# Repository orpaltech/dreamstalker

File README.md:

# dreamstalker

This device is designed to assist with lucid dreaming. The idea comes from this site: https://smartelectron.ru/projects/pribor-dlya-osoznannyh-snovidenij-dreamstalker-pro.

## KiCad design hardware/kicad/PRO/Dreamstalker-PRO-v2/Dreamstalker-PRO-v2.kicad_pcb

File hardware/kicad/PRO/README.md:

Dreamstalker PRO
------

The hardware to control your dreams. The author's resource is https://www.razrabotka.pro/single-post/pribor-dlya-osoznannyh-snovidenij-dreamstalker-pro

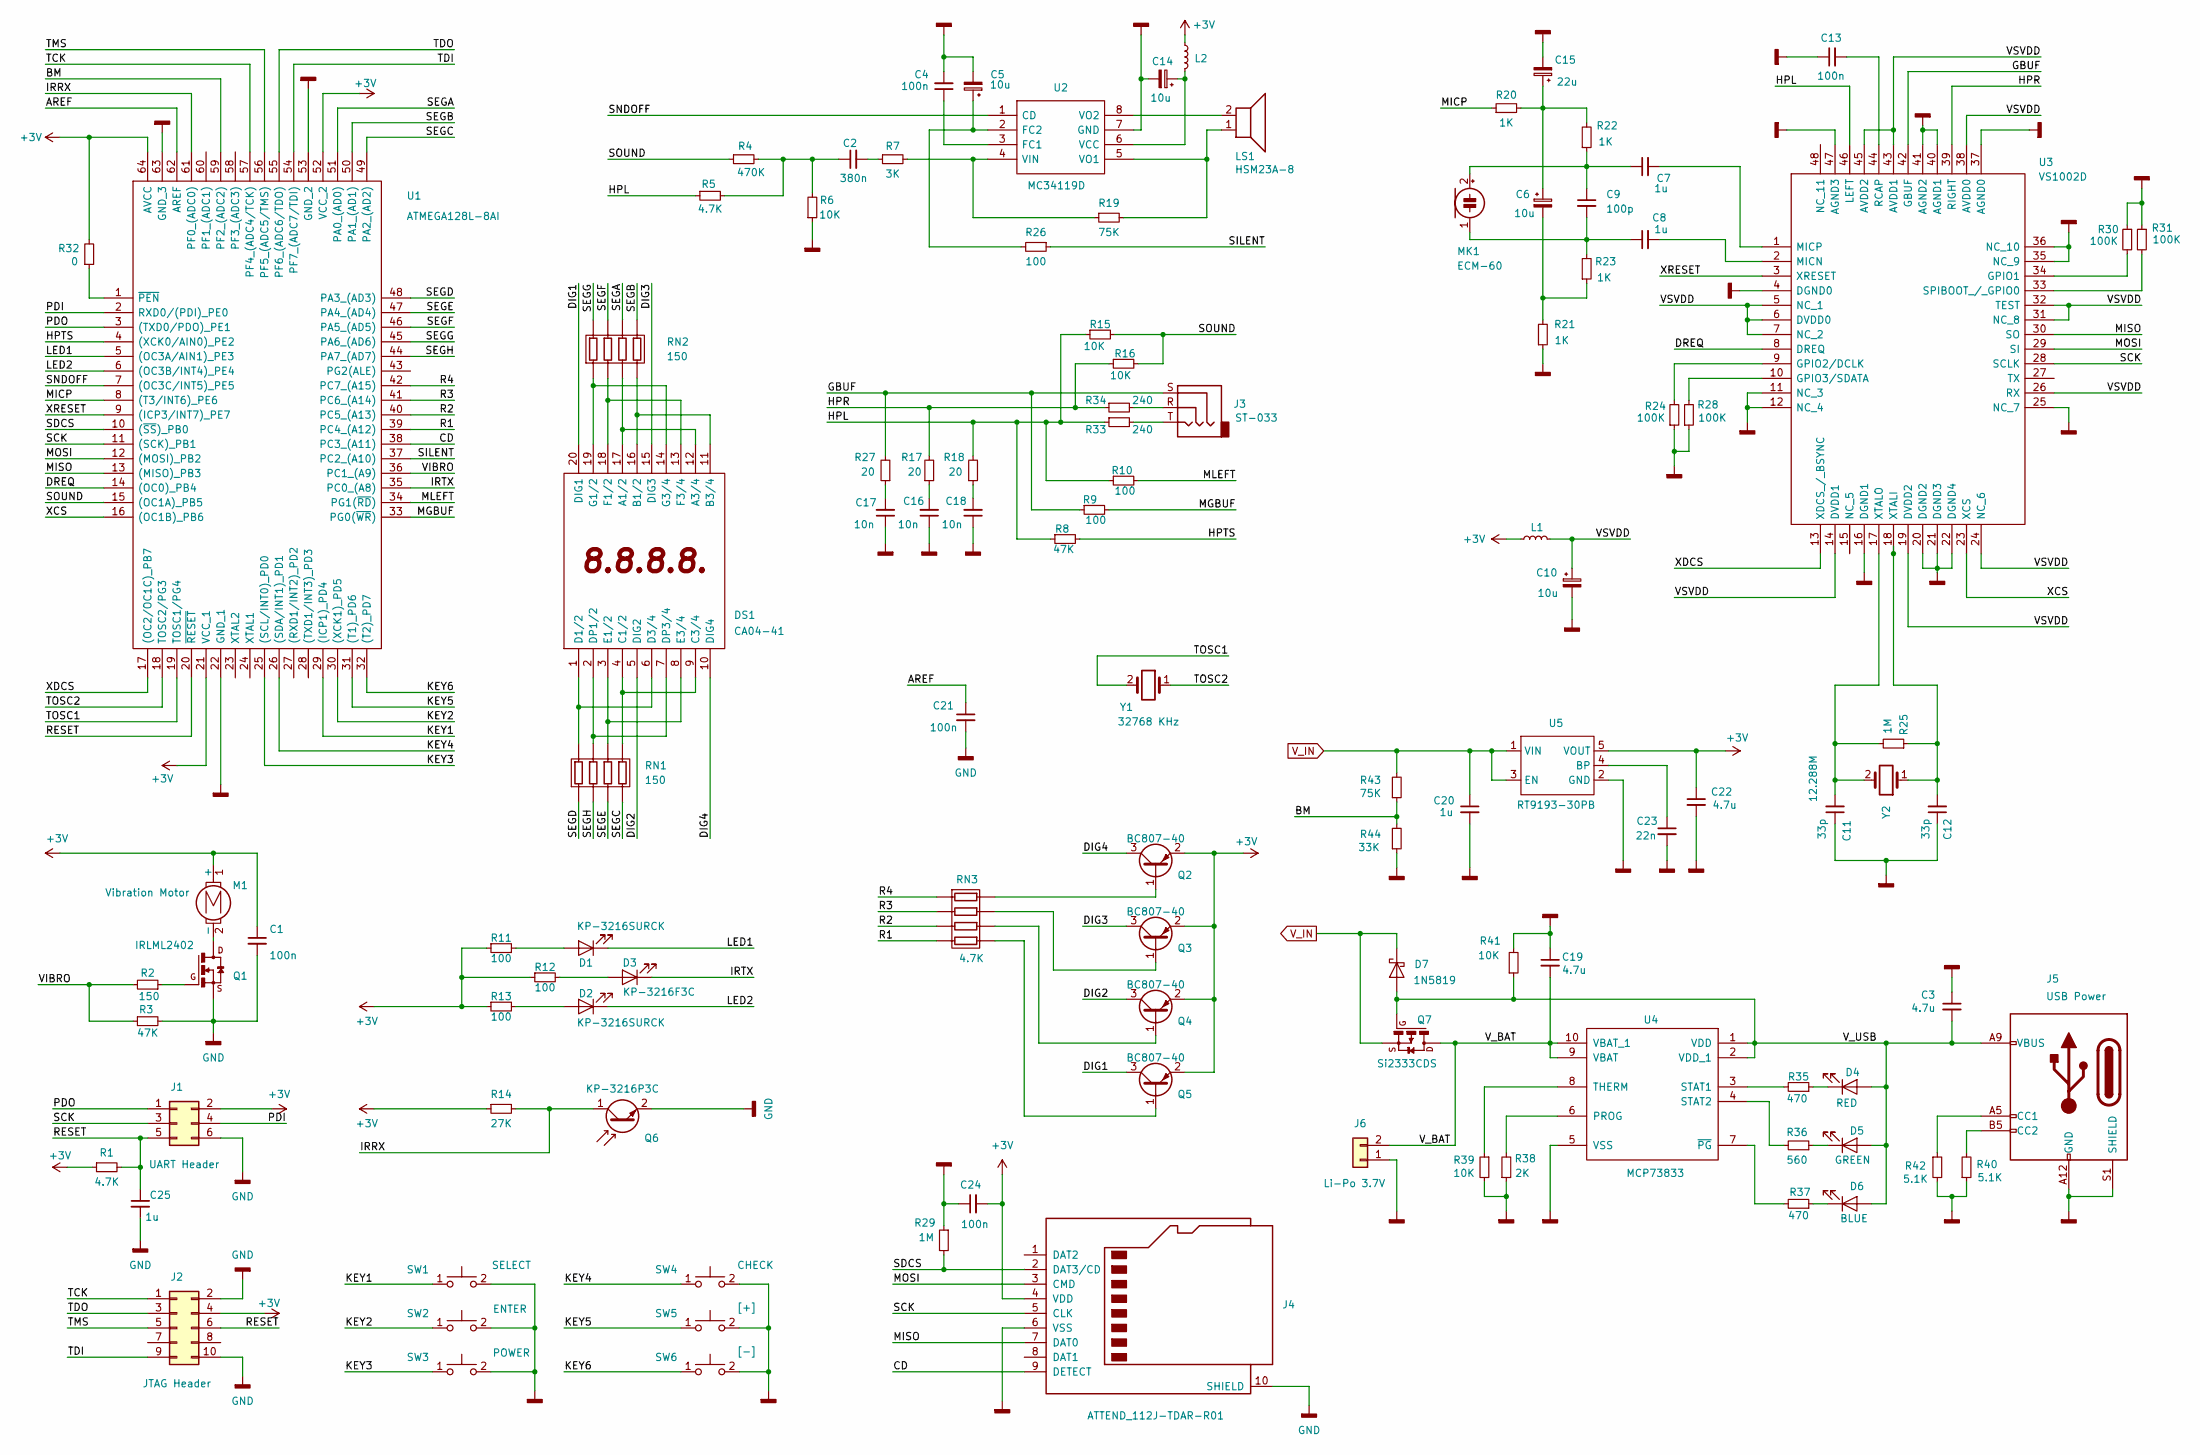
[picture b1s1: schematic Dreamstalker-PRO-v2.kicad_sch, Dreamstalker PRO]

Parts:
C1, C4, C13, C21, C24: 100n; C_0805_2012Metric
C2: 380n; C_0805_2012Metric
C3, C19, C22: 4.7u; C_0805_2012Metric
C5, C6, C10, C14: 10u; CP_EIA-3216-18_Kemet-A
C7, C8, C20, C25: 1u; C_0805_2012Metric
C9: 100p; C_0805_2012Metric
C11, C12: 33p; C_0805_2012Metric
C15: 22u; CP_EIA-3216-18_Kemet-A
C16, C17, C18: 10n; C_0805_2012Metric
C23: 22n; C_0805_2012Metric
D1, D2: KP-3216SURCK; LEDC3216X110N-TH
D3: KP-3216F3C; LEDC3216X110N-TH
D4: RED; LED_0805_2012Metric
D5: GREEN; LED_0805_2012Metric
D6: BLUE; LED_0805_2012Metric
D7: 1N5819; D_SOD-323_HandSoldering
DS1: CA04-41; Manufacturer_Part_Number CA04-41
J1: UART Header; PinHeader_2x03_P2.54mm_Vertical
J2: JTAG Header; PinHeader_2x05_P2.54mm_Vertical
J3: ST-033; DCI_Phone_Jack_3.5mm_ST-033
J4: ATTEND_112J-TDAR-R01; Manufacturer_Part_Number 112J-TDAR-R01
J5: USB Power; USB_C_Receptacle_GCT_USB4125-xx-x_6P_TopMnt_Horizontal
J6: Li-Po 3.7V; JST_PH_B2B-PH-K_1x02_P2.00mm_Vertical
L1, L2: L_Small; L_0805_2012Metric
LS1: HSM23A-8; Buzzer_23x11.5RM10
M1: Vibration Motor; VIBRO-MOTOR_SMD
MK1: ECM-60; JININ_ELECTRET_CONDENSER_MICROPHONE_ECM-60
Q1: IRLML2402; SOT95P237X112-3N
Q2, Q3, Q4, Q5: BC807-40; SOT95P230X110-3N
Q6: KP-3216P3C; LEDC3216X130N-TH
Q7: Si2333CDS; SOT-23
R1, R5: 4.7K; R_0603_1608Metric
R2: 150; R_0603_1608Metric
R3, R8: 47K; R_0603_1608Metric
R4: 470K; R_0603_1608Metric
R6, R15, R16, R39, R41: 10K; R_0603_1608Metric
R7: 3K; R_0603_1608Metric
R9, R10, R11, R12, R13, R26: 100; R_0603_1608Metric
R14: 27K; R_0603_1608Metric
R17, R18, R27: 20; R_0603_1608Metric
R19, R43: 75K; R_0603_1608Metric
R20, R21, R22, R23: 1K; R_0603_1608Metric
R24, R28, R30, R31: 100K; R_0603_1608Metric
R25, R29: 1M; R_0603_1608Metric
R32: 0; R_0603_1608Metric
R33, R34: 240; R_0603_1608Metric
R35, R37: 470; R_0603_1608Metric
R36: 560; R_0603_1608Metric
R38: 2K; L_0603_1608Metric
R40, R42: 5.1K; R_0603_1608Metric
R44: 33K; R_0603_1608Metric
RN1, RN2: 150; R_Array_Convex_4x0603
RN3: 4.7K; R_Array_Convex_4x0603
SW1: SELECT; SW_PUSH_6mm
SW2: ENTER; SW_PUSH_6mm
SW3: POWER; SW_PUSH_6mm
SW4: CHECK; SW_PUSH_6mm
SW5: [+]; SW_PUSH_6mm
SW6: [-]; SW_PUSH_6mm
U1: ATMEGA128L-8AI; QFP80P1600X1600X120-64N; Manufacturer_Part_Number ATMEGA128L-8AI
U2: MC34119D; SOIC127P600X175-8N; Manufacturer_Part_Number MC34119D
U3: VS1002D; QFP50P900X900X160-48N; Manufacturer_Part_Number VS1002D
U4: MCP73833; SOP50P490X110-10N; Manufacturer_Part_Number MCP73833-FCI/UN
U5: RT9193-30PB; SOT-23-5; Manufacturer_Part_Number RT9193
Y1: 32768 KHz; Crystal_SMD_3215-2Pin_3.2x1.5mm
Y2: 12.288M; Crystal_SMD_5032-2Pin_5.0x3.2mm

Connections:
+3V: C1.1, C22.1, C24.2, J1.2, J2.4, J4.4 (VDD), L1.1, L2.1, M1.1 (+), Q2.2 (E), Q3.2 (E), Q4.2 (E), Q5.2 (E), R1.1, R11.1, R12.1, R13.1, R14.1, R32.2, U1.21 (VCC_1), U1.52 (VCC_2), U1.64 (AVCC), U5.5 (VOUT)
/AREF: C21.1, U1.62 (AREF)
/BM: R43.1, R44.2, U1.59 (PF2_(ADC2))
/CD: J4.9 (DETECT), U1.38 (PC3_(A11))
/DIG1: DS1.20 (DIG1), Q5.3 (C)
/DIG2: DS1.5 (DIG2), Q4.3 (C)
/DIG3: DS1.15 (DIG3), Q3.3 (C)
/DIG4: DS1.10 (DIG4), Q2.3 (C)
/DREQ: U1.14 ((OC0)_PB4), U3.8 (DREQ)
/GBUF: J3.S, R9.1, R27.2, U3.42 (GBUF)
/HPL: R5.1, R8.1, R10.1, R15.1, R18.2, R33.1, U3.46 (LEFT)
/HPR: R16.1, R17.2, R34.1, U3.39 (RIGHT)
/HPTS: R8.2, U1.4 ((XCK0/AIN0)_PE2)
/IRRX: Q6.1 (C), R14.2, U1.61 (PF0_(ADC0))
/IRTX: D3.1 (K), U1.35 (PC0_(A8))
/KEY1: SW1.1, U1.29 ((ICP1)_PD4)
/KEY2: SW2.1, U1.30 ((XCK1)_PD5)
/KEY3: SW3.1, U1.25 ((SCL/INT0)_PD0)
/KEY4: SW4.1, U1.26 ((SDA/INT1)_PD1)
/KEY5: SW5.1, U1.31 ((T1)_PD6)
/KEY6: SW6.1, U1.32 ((T2)_PD7)
/LED1: D1.1 (K), U1.5 ((OC3A/AIN1)_PE3)
/LED2: D2.1 (K), U1.6 ((OC3B/INT4)_PE4)
/MGBUF: R9.2, U1.33 (PG0(~WR))
/MICP: R20.1, U1.8 ((T3/INT6)_PE6)
/MISO: J4.7 (DAT0), U1.13 ((MISO)_PB3), U3.30 (SO)
/MLEFT: R10.2, U1.34 (PG1(~RD))
/MOSI: J4.3 (CMD), U1.12 ((MOSI)_PB2), U3.29 (SI)
/PDI: J1.4, U1.2 (RXD0/(PDI)_PE0)
/PDO: J1.1, U1.3 ((TXD0/PDO)_PE1)
/R1: RN3.4 (R4.1), U1.39 (PC4_(A12))
/R2: RN3.3 (R3.1), U1.40 (PC5_(A13))
/R3: RN3.2 (R2.1), U1.41 (PC6_(A14))
/R4: RN3.1 (R1.1), U1.42 (PC7_(A15))
/RESET: C25.1, J1.5, J2.6, R1.2, U1.20 (~RESET)
/SCK: J1.3, J4.5 (CLK), U1.11 ((SCK)_PB1), U3.28 (SCLK)
/SDCS: J4.2 (DAT3/CD), R29.2, U1.10 ((~SS)_PB0)
/SEGA: RN2.6 (R3.2), U1.51 (PA0_(AD0))
/SEGB: RN2.5 (R4.2), U1.50 (PA1_(AD1))
/SEGC: RN1.4 (R4.1), U1.49 (PA2_(AD2))
/SEGD: RN1.1 (R1.1), U1.48 (PA3_(AD3))
/SEGE: RN1.3 (R3.1), U1.47 (PA4_(AD4))
/SEGF: RN2.7 (R2.2), U1.46 (PA5_(AD5))
/SEGG: RN2.8 (R1.2), U1.45 (PA6_(AD6))
/SEGH: RN1.2 (R2.1), U1.44 (PA7_(AD7))
/SILENT: R26.1, U1.37 (PC2_(A10))
/SNDOFF: U1.7 ((OC3C/INT5)_PE5), U2.1 (CD)
/SOUND: R4.1, R15.2, R16.2, U1.15 ((OC1A)_PB5)
/TCK: J2.1, U1.57 (PF4_(ADC4/TCK))
/TDI: J2.9, U1.54 (PF7_(ADC7/TDI))
/TDO: J2.3, U1.55 (PF6_(ADC6/TDO))
/TMS: J2.5, U1.56 (PF5_(ADC5/TMS))
/TOSC1: U1.19 (TOSC1/PG4), Y1.2
/TOSC2: U1.18 (TOSC2/PG3), Y1.1
/VIBRO: R2.2, R3.1, U1.36 (PC1_(A9))
/VSVDD: C10.1, L1.2, U3.5 (NC_1), U3.6 (DVDD0), U3.7 (NC_2), U3.14 (DVDD1), U3.19 (DVDD2), U3.24 (NC_6), U3.26 (RX), U3.31 (NC_8), U3.32 (TEST), U3.38 (AVDD0), U3.43 (AVDD1), U3.45 (AVDD2)
/V_BAT: C19.2, J6.2, Q7.3 (D), U4.9 (VBAT), U4.10 (VBAT_1)
/V_USB: C3.2, D4.2 (A), D5.2 (A), D6.2 (A), D7.2 (A), J5.A9 (VBUS), J5.B9 (VBUS), Q7.1 (G), R41.1, U4.1 (VDD), U4.2 (VDD_1)
/XCS: U1.16 ((OC1B)_PB6), U3.23 (XCS)
/XDCS: U1.17 ((OC2/OC1C)_PB7), U3.13 (XDCS_/_BSYNC)
/XRESET: U1.9 ((ICP3/INT7)_PE7), U3.3 (XRESET)
GND: C1.2, C3.1, C4.2, C5.2, C10.2, C11.1, C12.1, C13.1, C14.2, C15.2, C16.1, C17.1, C18.1, C19.1, C20.2, C21.2, C22.2, C23.2, C24.1, C25.2, J1.6, J2.2, J2.10, J4.6 (VSS), J4.10 (SHIELD), J5.A12 (GND), J5.B12 (GND), J5.S1 (SHIELD), J6.1, Q1.2 (S), Q6.2 (E), R3.2, R6.1, R21.1, R24.1, R28.1, R29.1, R30.1, R31.1, R38.1, R39.2, R40.1, R41.2, R42.2, R44.1, SW1.2, SW2.2, SW3.2, SW4.2, SW5.2, SW6.2, U1.22 (GND_1), U1.53 (GND_2), U1.63 (GND_3), U2.7 (GND), U3.4 (DGND0), U3.11 (NC_3), U3.12 (NC_4), U3.16 (DGND1), U3.20 (DGND2), U3.21 (DGND3), U3.22 (DGND4), U3.25 (NC_7), U3.35 (NC_9), U3.36 (NC_10), U3.37 (AGND0), U3.40 (AGND1), U3.41 (AGND2), U3.47 (AGND3), U4.5 (VSS), U5.2 (GND)
unnamed: C2.1, R4.2, R5.2, R6.2
unnamed: C2.2, R7.1
unnamed: C6.2, R21.2, R23.1
unnamed: C6.1, C15.1, R20.2, R22.2
unnamed: C16.2, R17.1
unnamed: C17.2, R27.1
unnamed: C18.2, R18.1
unnamed: D1.2 (A), R11.2
unnamed: D2.2 (A), R13.2
unnamed: D3.2 (A), R12.2
unnamed: D4.1 (K), R35.1
unnamed: D5.1 (K), R36.1
unnamed: D6.1 (K), R37.1
unnamed: DS1.12 (A3/4), DS1.17 (A1/2), RN2.3 (R3.1)
unnamed: DS1.11 (B3/4), DS1.16 (B1/2), RN2.4 (R4.1)
unnamed: DS1.4 (C1/2), DS1.9 (C3/4), RN1.5 (R4.2)
unnamed: DS1.1 (D1/2), DS1.6 (D3/4), RN1.8 (R1.2)
unnamed: DS1.2 (DP1/2), DS1.7 (DP3/4), RN1.7 (R2.2)
unnamed: DS1.3 (E1/2), DS1.8 (E3/4), RN1.6 (R3.2)
unnamed: DS1.13 (F3/4), DS1.18 (F1/2), RN2.2 (R2.1)
unnamed: DS1.14 (G3/4), DS1.19 (G1/2), RN2.1 (R1.1)
unnamed: J3.R, R34.2
unnamed: J3.T, R33.2
unnamed: J5.A5 (CC1), R42.1
unnamed: J5.B5 (CC2), R40.2
unnamed: M1.2 (-), Q1.3 (D)
unnamed: C7.1, C9.1, MK1.2 (+), R22.1
unnamed: C8.1, C9.2, MK1.1 (-), R23.2
unnamed: Q1.1 (G), R2.1
unnamed: Q2.1 (B), RN3.8 (R1.2)
unnamed: Q3.1 (B), RN3.7 (R2.2)
unnamed: Q4.1 (B), RN3.6 (R3.2)
unnamed: Q5.1 (B), RN3.5 (R4.2)
unnamed: R32.1, U1.1 (~PEN)
unnamed: C4.1, U2.3 (FC1)
unnamed: C5.1, R26.2, U2.2 (FC2)
unnamed: C14.1, L2.2, U2.6 (VCC)
unnamed: R7.2, R19.1, U2.4 (VIN)
unnamed: LS1.1, R19.2, U2.5 (VO1)
unnamed: LS1.2, U2.8 (VO2)
unnamed: R30.2, U3.34 (GPIO1)
unnamed: R24.2, U3.9 (GPIO2/DCLK)
unnamed: R28.2, U3.10 (GPIO3/SDATA)
unnamed: C8.2, U3.2 (MICN)
unnamed: C7.2, U3.1 (MICP)
unnamed: C13.2, U3.44 (RCAP)
unnamed: R31.2, U3.33 (SPIBOOT_/_GPIO0)
unnamed: C12.2, R25.1, U3.18 (XTALI), Y2.1
unnamed: C11.2, R25.2, U3.17 (XTALO), Y2.2
unnamed: R38.2, U4.6 (PROG)
unnamed: R35.2, U4.3 (STAT1)
unnamed: R36.2, U4.4 (STAT2)
unnamed: R39.1, U4.8 (THERM)
unnamed: R37.2, U4.7 (~PG)
unnamed: C23.1, U5.4 (BP)
V_IN: C20.1, D7.1 (K), Q7.2 (S), R43.2, U5.1 (VIN), U5.3 (EN)

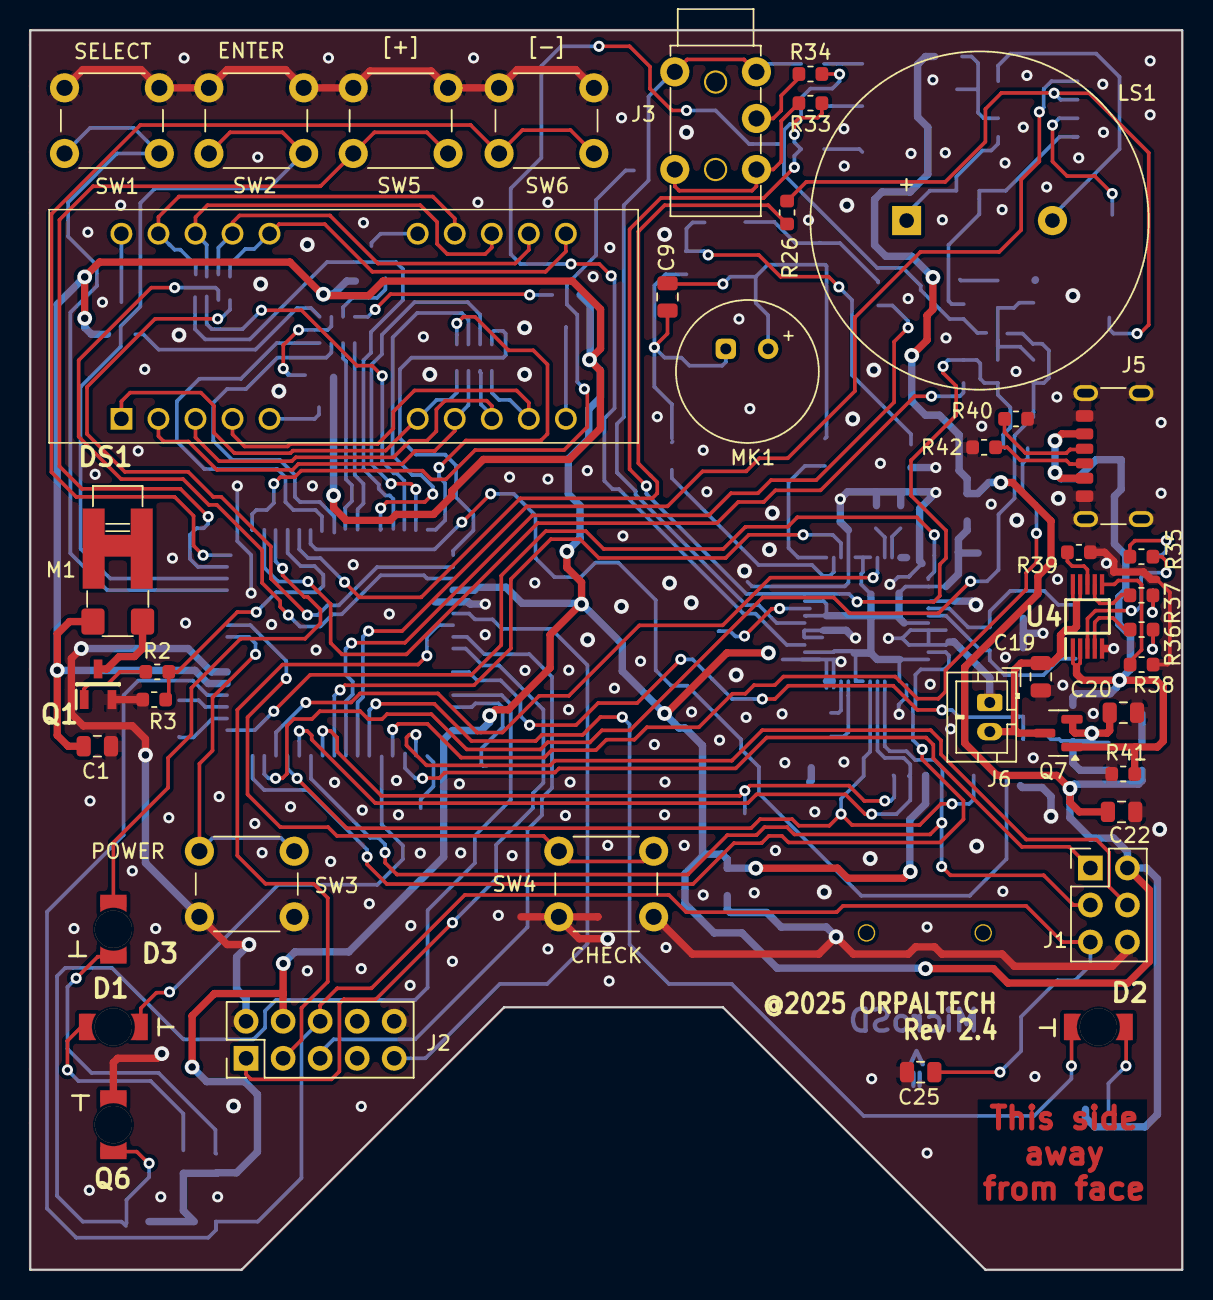
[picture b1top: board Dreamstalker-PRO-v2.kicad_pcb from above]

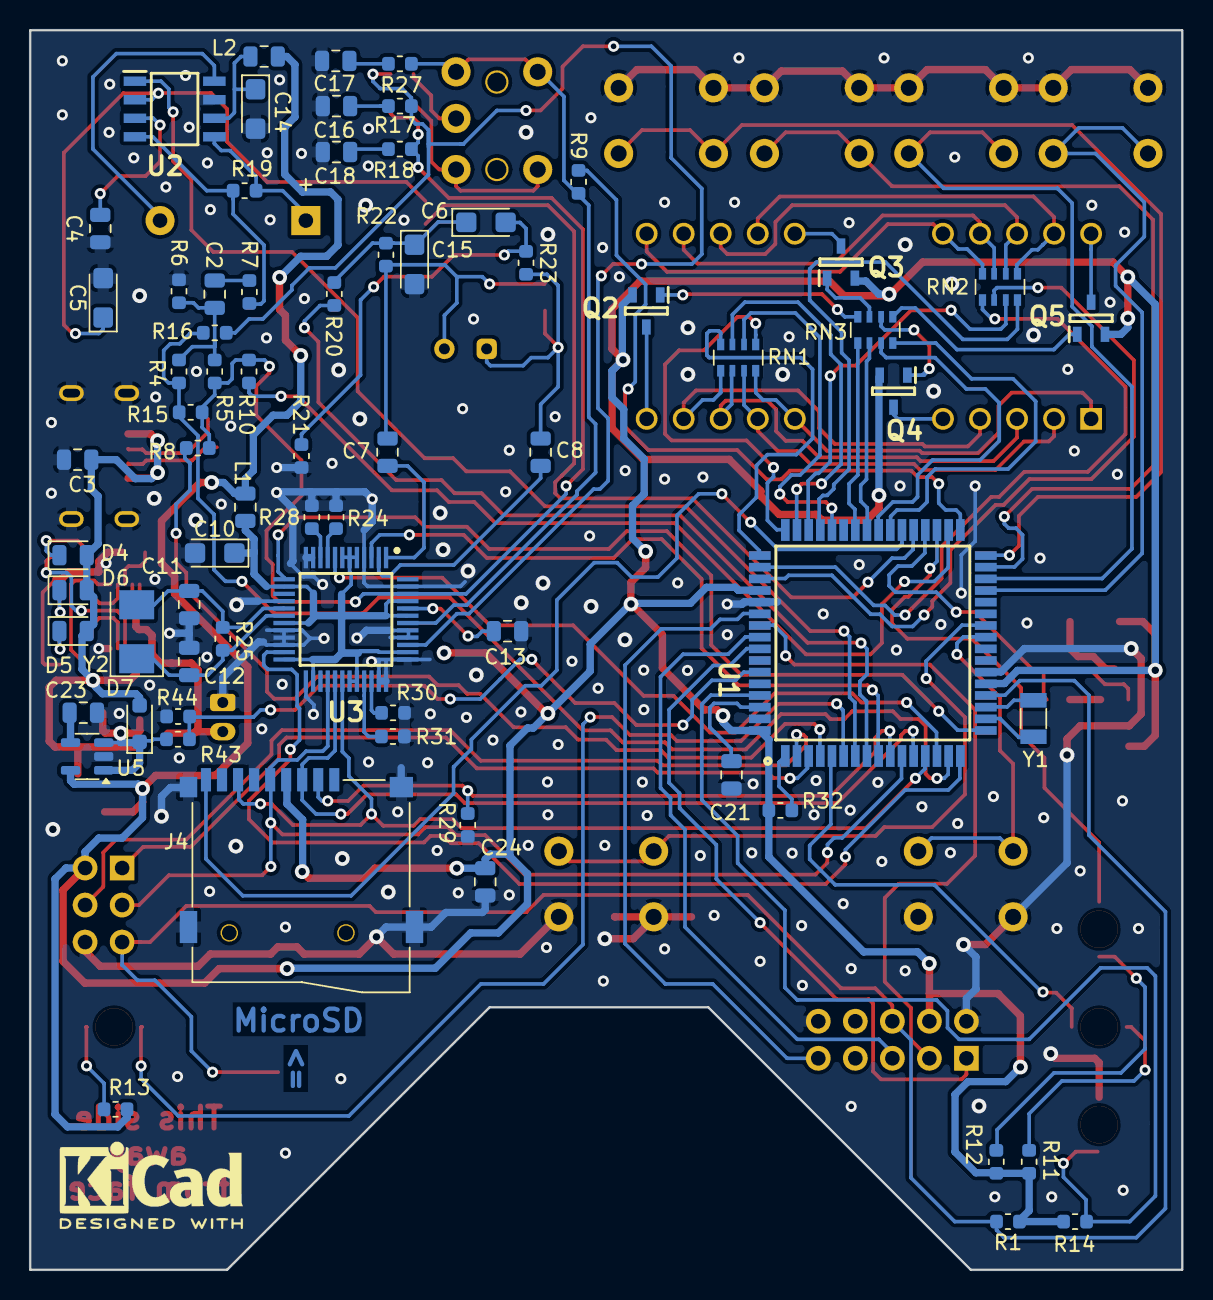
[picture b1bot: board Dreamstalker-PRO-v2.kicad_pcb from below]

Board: 2 copper layers, 79.0 x 85.0 mm, 111 parts (70 on the bottom side), 118 nets.

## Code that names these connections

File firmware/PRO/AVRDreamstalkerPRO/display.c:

/*
 * This file is part of the AVR Dreamstalker software
 * (https://github.com/orpaltech/dreamstalker).
 *
 * Copyright (c) 2013-2019	ORPAL Technologies, Inc.
 *
 * This program is free software: you can redistribute it and/or modify
 * it under the terms of the GNU General Public License as published by
 * the Free Software Foundation, version 3.
 *
 * This program is distributed in the hope that it will be useful, but
 * WITHOUT ANY WARRANTY; without even the implied warranty of
 * MERCHANTABILITY or FITNESS FOR A PARTICULAR PURPOSE. See the GNU
 * General Public License for more details.
 *
 * You should have received a copy of the GNU General Public License
 * along with this program. If not, see <http://www.gnu.org/licenses/>.
 */

#include <util/delay.h>
#include <stdio.h>
#include <string.h>
#include <avr/io.h>
#include <avr/interrupt.h>
#include <avr/pgmspace.h>

#include "display.h"
#include "rtclock.h"
//#include "timers.h"
#include "dreamstalker.h"

/* Peripheral controls (Platform dependent) */
#define DD_DIG1		_BV(DDC4)
#define DD_DIG2		_BV(DDC5)
#define DD_DIG3		_BV(DDC6)
#define DD_DIG4		_BV(DDC7)

#define BIT_DIG1		PC4
#define BIT_DIG2		PC5
#define BIT_DIG3		PC6
#define BIT_DIG4		PC7

#define DIG1		_BV(BIT_DIG1)
#define DIG2		_BV(BIT_DIG2)
#define DIG3		_BV(BIT_DIG3)
#define DIG4		_BV(BIT_DIG4)

#define SEGA		_BV(PA0)
#define SEGB		_BV(PA1)
#define SEGC		_BV(PA2)
#define SEGD		_BV(PA3)
#define SEGE		_BV(PA4)
#define SEGF		_BV(PA5)
#define SEGG		_BV(PA6)
#define SEGH		_BV(PA7)

#define DDR_SEG			DDRA
#define DDR_DIG			DDRC
#define PORT_SEG		PORTA
#define PORT_DIG		PORTC


/*-----------------------------------------------------------------------*/
PROGMEM const uint8_t num_code[] = {
	/*0*/ SEGA	| SEGB	| SEGC	| SEGD	| SEGE	| SEGF,
	/*1*/		  SEGB	| SEGC,
	/*2*/ SEGA	| SEGB			| SEGD	| SEGE			| SEGG,
	/*3*/ SEGA	| SEGB	| SEGC	| SEGD					| SEGG,
	/*4*/ 		  SEGB	| SEGC					| SEGF	| SEGG,
	/*5*/ SEGA			| SEGC	| SEGD			| SEGF	| SEGG,
	/*6*/ SEGA			| SEGC	| SEGD	| SEGE	| SEGF	| SEGG,
	/*7*/ SEGA	| SEGB	| SEGC,
	/*8*/ SEGA	| SEGB	| SEGC	| SEGD	| SEGE	| SEGF	| SEGG,
	/*9*/ SEGA	| SEGB	| SEGC	| SEGD			| SEGF	| SEGG,
	/*A*/ SEGA	| SEGB	| SEGC			| SEGE	| SEGF	| SEGG,
	/*b*/				  SEGC	| SEGD	| SEGE	| SEGF	| SEGG,
	/*C*/ SEGA					| SEGD	| SEGE	| SEGF,
	/*d*/		  SEGB	| SEGC	| SEGD	| SEGE			| SEGG,
	/*E*/ SEGA					| SEGD	| SEGE	| SEGF	| SEGG,
	/*F*/ SEGA							| SEGE	| SEGF	| SEGG,
};

PROGMEM const uint8_t ascii_code[] = {
	0,0,0,0,0,0,0,0,0,0,
	0,0,0,0,0,0,0,0,0,0,
	0,0,0,0,0,0,0,0,0,0,
	0,0,
	/* */ 0,
	0,0,0,0,0,0,0,
	0,0,0,0,0,
	/*-*/ 												  SEGG,
	/*.*/														  SEGH,
	0,
	/*0*/ SEGA	| SEGB	| SEGC	| SEGD	| SEGE	| SEGF,
	/*1*/		  SEGB	| SEGC,
	/*2*/ SEGA	| SEGB			| SEGD	| SEGE			| SEGG,
	/*3*/ SEGA	| SEGB	| SEGC	| SEGD					| SEGG,
	/*4*/ 		  SEGB	| SEGC					| SEGF	| SEGG,
	/*5*/ SEGA			| SEGC	| SEGD			| SEGF	| SEGG,
	/*6*/ SEGA			| SEGC	| SEGD	| SEGE	| SEGF	| SEGG,
	/*7*/ SEGA	| SEGB	| SEGC,
	/*8*/ SEGA	| SEGB	| SEGC	| SEGD	| SEGE	| SEGF	| SEGG,
	/*9*/ SEGA	| SEGB	| SEGC	| SEGD			| SEGF	| SEGG,
	0,0,0,0,0,0,0,
	/*A*/ SEGA	| SEGB	| SEGC			| SEGE	| SEGF	| SEGG,
	/*B*/ 0,
	/*C*/ SEGA					| SEGD	| SEGE	| SEGF,
	/*D*/ 0,
	/*E*/ SEGA					| SEGD	| SEGE	| SEGF	| SEGG,
	/*F*/ SEGA							| SEGE	| SEGF	| SEGG,
	/*G*/ SEGA			| SEGC	| SEGD	| SEGE	| SEGF,
	/*H*/ 		  SEGB	| SEGC			| SEGE	| SEGF	| SEGG,
	/*I*/		  SEGB	| SEGC,
	/*J*/ 		  SEGB	| SEGC	| SEGD,
	/*K*/ 0,
	/*L*/ 						  SEGD	| SEGE	| SEGF,
	/*M*/ 0,
	/*N*/ 0,
	/*O*/ SEGA	| SEGB	| SEGC	| SEGD	| SEGE	| SEGF,
	/*P*/ SEGA	| SEGB					| SEGE	| SEGF	| SEGG,
	/*Q*/ 0,
	/*R*/ 0,
	/*S*/ SEGA			| SEGC	| SEGD			| SEGF	| SEGG,
	/*T*/ 0,
	/*U*/ 		  SEGB	| SEGC	| SEGD	| SEGE	| SEGF,
	/*V*/ 0,
	/*W*/ 0,
	/*X*/ 0,
	/*Y*/ 0,
	/*Z*/ 0,
	0,0,0,0,
	/*_*/						  SEGD,
	0,
	/*a*/ 0,
	/*b*/ 				  SEGC	| SEGD	| SEGE	| SEGF	| SEGG,
	/*c*/						  SEGD	| SEGE			| SEGG,
	/*d*/ 		SEGB	| SEGC	| SEGD	| SEGE			| SEGG,
	/*e*/ 0,
	/*f*/ 0,
	/*g*/ SEGA	| SEGB	| SEGC	| SEGD			| SEGF	| SEGG,
	/*h*/ 				  SEGC			| SEGE	| SEGF	| SEGG,
	/*i*/ 0,
	/*j*/ 0,
	/*k*/ 0,
	/*l*/ 0,
	/*m*/ 0,
	/*n*/ 				  SEGC			| SEGE			| SEGG,
	/*o*/				  SEGC	| SEGD	| SEGE			| SEGG,
	/*p*/ SEGA	| SEGB					| SEGE	| SEGF	| SEGG,
	/*q*/ SEGA	| SEGB	| SEGC					| SEGF	| SEGG,
	/*r*/ 									SEGE		| SEGG,
	/*s*/ 0,
	/*t*/						  SEGD	| SEGE	| SEGF	| SEGG,
	/*u*/ 				  SEGC	| SEGD	| SEGE,
	/*v*/ 0,
	/*w*/ 0,
	/*x*/ 0,
	/*y*/ 		  SEGB	| SEGC	| SEGD			| SEGF	| SEGG,
	/*z*/ 0,
};

/*-----------------------------------------------------------------------*/
static volatile uint8_t counter = 0;
static volatile uint8_t seg_data[4] = {0x00,0x00,0x00,0x00};
static uint8_t digits[4] = {DIG1,DIG2,DIG3,DIG4};

/*-----------------------------------------------------------------------*/
static
void disp_pins_off()
{
	PORT_DIG |= (DIG1 | DIG2 | DIG3 | DIG4);	// switch-off digits
	PORT_SEG |= 0xFF;							// switch-off segments
}

void disp_isr (void)
{
	disp_pins_off();

	PORT_DIG &= ~digits[counter];
	PORT_SEG &= ~seg_data[counter];	/* Write code */
	counter = (counter + 1) % 4;	/* Increment digit counter */
}

static
void disp_timer_on()
{
	//timer2_on(disp_isr, 1);
}

static
void disp_timer_off()
{
	//timer2_off(disp_isr);
}

static
uint8_t get_num_code(int index)
{
	return pgm_read_byte(&(num_code[index]));
}

static
uint8_t get_ascii_code(int index)
{
	return pgm_read_byte(&(ascii_code[index]));
}

static
void wait_cycle (void)
{
	_delay_ms(disp_get_cycle_ms());
}


/*-----------------------------------------------------------------------*/

void disp_init (void)
{
	DDR_SEG |= 0xFF;									// segment outputs
	DDR_DIG |= (DD_DIG1 | DD_DIG2 | DD_DIG3 | DD_DIG4);	// digit outputs

	disp_on();
}

void disp_on (void)
{
	disp_pins_off();

	wait_cycle();

	disp_timer_on();
}

void disp_off (void)
{
	disp_timer_off();

	wait_cycle();

	disp_pins_off();
}

int disp_get_cycle_ms(void)
{
	return RTC_INTERVAL_MSEC;
}

void disp_clear (void)
{
	seg_data[0] = 0;
	seg_data[1] = 0;
	seg_data[2] = 0;
	seg_data[3] = 0;
}

void disp_text(const char *text)
{
	int len, pos, i;

	len = strlen(text);
	if (len==0)
		return;

	for (i=0; i<4; i++)
		seg_data[i] = 0;

	for (i=0,pos=0; pos<len; pos++) {
		if(i>0 && text[pos]=='.') {
			seg_data[i-1] |= SEGH;
		} else {
			if(i<4) {
				seg_data[i] = get_ascii_code((int)text[pos]);
				i++;
			} else
				break;
		}
	}
}

void disp_version (char type, uint16_t ver, int cycles)
{
	char msg[6];

	snprintf(msg, 6, "%c%01u.%02u", type, VER_MAJOR(ver), VER_MINOR(ver));
	disp_msg(msg, cycles);
}

void disp_hex(uint16_t num)
{
	seg_data[3] = get_num_code((num >> 0) & 0xF);
	seg_data[2] = get_num_code((num >> 4) & 0xF);
	seg_data[1] = get_num_code((num >> 8) & 0xF);
	seg_data[0] = get_num_code((num >> 12) & 0xF);

	wait_cycle();
}

void disp_dec (uint16_t num)
{
	char msg[5];

	if (num>9999)
		strcpy(msg, "EEEE");
	else
		snprintf(msg, 5, "%4u", num);
	disp_msg(msg, 1);
}

/*
 * Displays first 4 symbols of the text
 */
void disp_msg(const char *text, int cycles)
{
	disp_text(text);

	if (cycles < 1)
		cycles = 1;
	while (--cycles>=0)
		wait_cycle();
}

void disp_flag (int flag_val)
{
	if (flag_val)
		disp_msg("  On", 1);
	else
		disp_msg(" OFF", 1);
}

void disp_wakeup_timer_delay (void)
{
	uint8_t hour, minute;
	uint16_t delay;
	char msg[6];

	if (is_invalid_wakeup_timer_delay())
		strcpy(msg, " OFF");
	else {
		delay = get_wakeup_timer_delay();
		hour = delay / 60;
		minute = delay - (hour * 60);
		snprintf(msg, 6, "%02u.%02u", hour, minute);
	}

	disp_text(msg);
}

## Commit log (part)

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2019-08-21 Added readme
2019-08-25 Planned update
2019-09-08 Added Ultra
2019-11-16 Dreamstalker-PRO PCB improvements
2020-04-11 Remove zip files
2020-04-11 Add PRO firmware sources
2024-04-14 DSPRO firmware update
2024-06-08 Planned changes
2024-06-08 Removed build folder
2025-02-26 PRO: Add most recent firmware
2025-03-17 Add kicad pcb PRO v2
2025-03-17 Update auto-generated files
2025-03-17 PRO: Update kicad files
2025-12-10 1) Fixed: battery monitor not able to detect low-battery state (Now get battery monitor signal from LDO input). 2) Other planned updates.
2025-12-30 Moved from virtual functions to callbacks
2025-12-30 Tools: add console remd-sample receiver
2025-12-30 Set ADC sample rate to 1KHz for any number of running channels
2026-01-02 Renamed some classes; Updated OCRx registry settings
2026-01-09 REM detector test mode will write to a file instead of serial port; Add desktop manager tool
2026-01-26 REM detection algorithm updates; ADPCM recording fix
2026-01-26 Remove unused files
2026-01-26 Kicad updates; Minor changes to sources
2026-02-02 New REM detect algorithm; New visualization in qtdreamflowmanager; Lots of bugfix
2026-02-04 Move images under PRO folder
